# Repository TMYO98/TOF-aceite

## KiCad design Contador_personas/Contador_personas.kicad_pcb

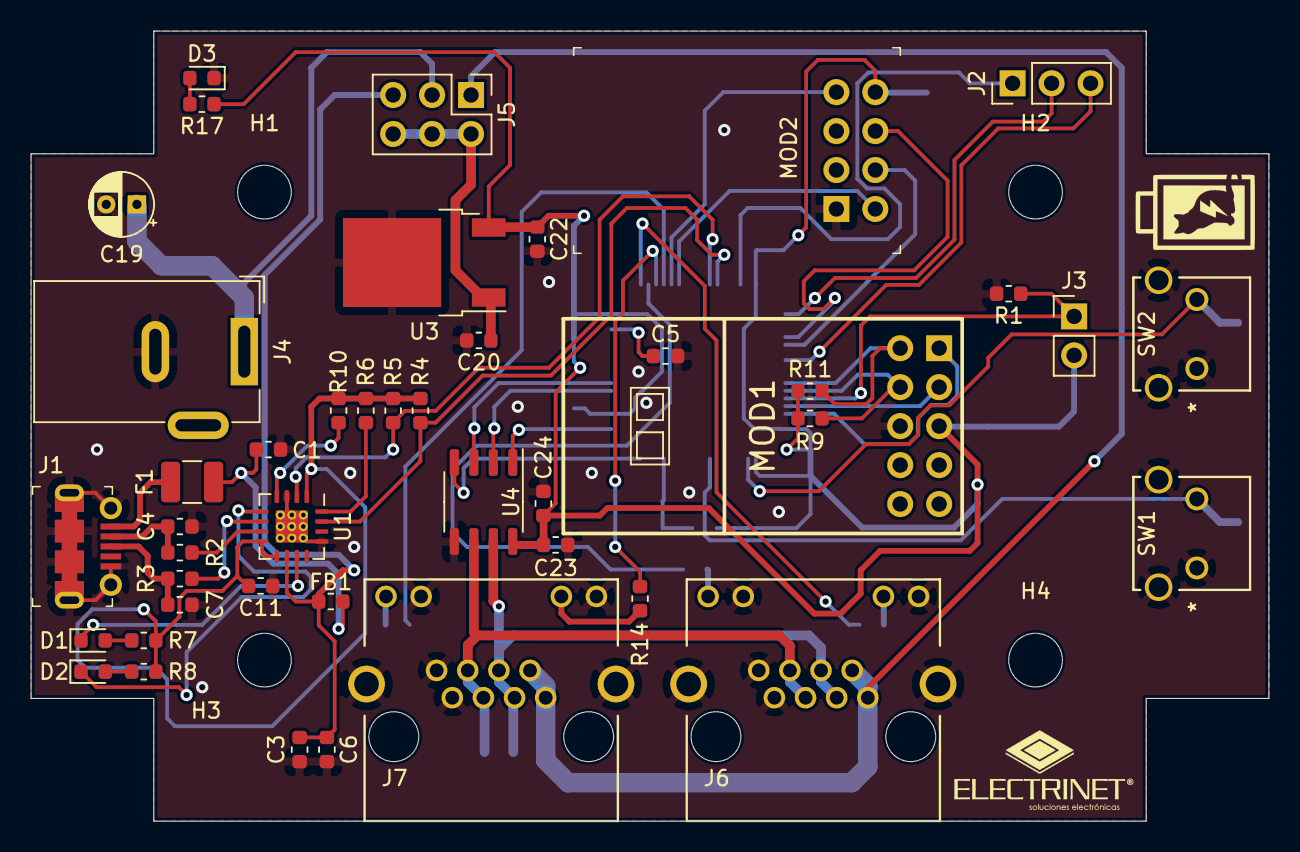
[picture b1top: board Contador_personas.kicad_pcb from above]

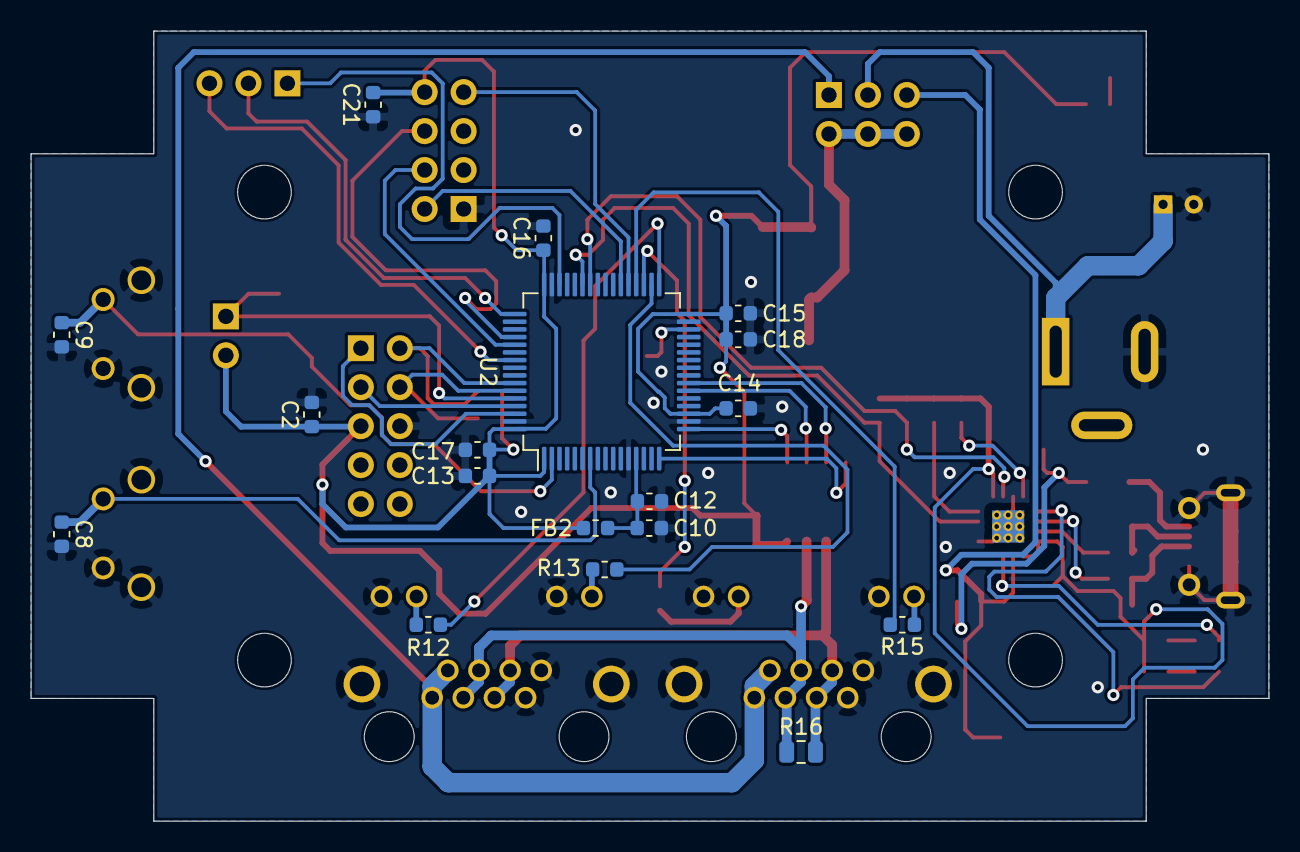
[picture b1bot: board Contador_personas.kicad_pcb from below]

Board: 2 copper layers, 80.7 x 51.5 mm, 66 parts (18 on the bottom side), 52 nets.

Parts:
C1: 10nF; C_0603_1608Metric
C2, C6, C8, C9, C10, C11, C12, C13, C14, C15, C16, C17, C21, C24: 0.1uF; C_0603_1608Metric
C3, C5, C18: 4.7uF; C_0603_1608Metric
C4, C7: 47pF; C_0603_1608Metric
C19: 10uF; CP_Radial_D4.0mm_P2.00mm
C20, C23: 1uF; C_0603_1608Metric
C22: 2.2uF; C_0603_1608Metric
D1, D2, D3: LED; LED_0603_1608Metric
F1: 0ZCH0050FF2G; Fuse_1210_3225Metric
FB1: BLM21PG221SN1D; R_0603_1608Metric
FB2: BK1608TS601-T; R_0603_1608Metric
H1, H2, H3, H4: MountingHole; MountingHole_3.5mm
J1: 1050170001; USB_Micro_B_Female_1050170001
J2: Conn_01x03_Male; PinHeader_1x03_P2.54mm_Vertical
J3: Conn_01x02_Male; PinHeader_1x02_P2.54mm_Vertical
J4: 694106301002‎; BarrelJack_Wuerth_6941xx301002
J5: Conn_02x03_Odd_Even; PinHeader_2x03_P2.54mm_Vertical
J6, J7: RJHSE-5381
MOD1: VL53L1X-SATEL; VL53L1X_SATEL
MOD2: WRL-17146; Wifi_Module_ESP8266_WRL-13678
R1, R4, R5, R6, R10: 10K; R_0603_1608Metric
R2, R3: 27; R_0603_1608Metric
R7, R8, R12, R13, R14, R15: 270; R_0603_1608Metric
R9, R11: 4.7K; R_0603_1608Metric
R16: 120; R_0805_2012Metric
R17: 1K; R_0603_1608Metric
SW1, SW2: 1825027-5
U1: FT230XQ; QFN-16-1EP_4x4mm_P0.65mm_EP2.1x2.1mm_ThermalVias
U2: STM32F401RETx; LQFP-64_10x10mm_P0.5mm
U3: LDF33DT-TR; TO-252-2
U4: ST3485EIDT‎; SO-8_3.9x4.9mm_P1.27mm

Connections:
+3V3: C2.1, C13.1, C14.1, C15.1, C16.1, C17.1, C18.2, C21.2, C22.1, C23.1, C24.1, FB2.2, J3.2, MOD1.5, MOD2.8, R9.1, R11.1, R17.1, U2.1, U2.19, U2.32, U2.48, U2.64, U3.3, U4.8
+5V: C3.1, C6.1, FB1.1, J5.5, U1.10
+9V: C19.1, J4.1, J5.3
+12V: J5.1, J6.1, J6.2, J7.1, J7.2
+VDC: C20.1, J5.2, J5.4, J5.6, U3.1
A: J6.5, J6.6, J7.5, J7.6, R16.2, U4.6
B: J6.3, J6.4, J7.3, J7.4, R16.1, U4.7
CHPD: MOD2.4, U2.53
DE: U2.23, U4.3
GND: C1.2, C2.2, C3.2, C4.2, C5.2, C6.2, C7.2, C8.2, C9.2, C10.2, C11.1, C12.2, C13.2, C14.2, C15.2, C16.2, C17.2, C18.1, C19.2, C20.2, C21.1, C22.2, C23.2, C24.2, D3.1, J1.5, J1.SH, J4.2, J6.7, J6.8, J6.9, J6.11, J6.S1, J6.S2, J7.7, J7.8, J7.9, J7.11, J7.S1, J7.S2, MOD1.6, MOD2.1, R1.2, SW1.1, SW1.3, SW1.4, SW2.1, SW2.3, SW2.4, U1.3, U1.13, U1.17, U2.12, U2.18, U2.31, U2.47, U2.63, U3.2, U4.5
I2C1_SCL: MOD1.2, R11.2, U2.58
I2C1_SDA: MOD1.4, R9.2, U2.59
INT: MOD1.1, U2.62
LED_1_DI: R12.2, U2.33
LED_1_DO: R13.2, U2.34
LED_2_DI: R14.2, U2.35
LED_2_DO: R15.2, U2.36
unnamed: C1.1, F1.1, FB1.2
unnamed: C4.1, J1.2, R2.2
unnamed: C5.1, U2.30
unnamed: C7.1, J1.3, R3.2
unnamed: C8.1, SW1.2, U2.7
unnamed: C9.1, SW2.2, U2.2
unnamed: C10.1, C12.1, FB2.1, U2.13
unnamed: C11.2, R4.1, R5.1, R6.1, R7.1, R8.1, R10.1, U1.1, U1.8, U1.9
unnamed: D1.1, U1.11
unnamed: D1.2, R7.2
unnamed: D2.1, U1.5
unnamed: D2.2, R8.2
unnamed: D3.2, R17.2
unnamed: F1.2, J1.1
unnamed: J3.1, R1.1, U2.60
unnamed: J6.10, R12.1
unnamed: J6.12, R13.1
unnamed: J7.10, R14.1
unnamed: J7.12, R15.1
unnamed: R2.1, U1.7
unnamed: R3.1, U1.6
unnamed: R6.2, U1.16
unnamed: R10.2, U1.4
RST: MOD2.6, U2.52
SWCLK: J2.2, U2.49
SWDIO: J2.1, U2.46
SWO: J2.3, U2.55
USART1_RX: R4.2, U1.15, U2.43
USART1_TX: R5.2, U1.2, U2.42
USART2_RX: U2.17, U4.1
USART2_TX: U2.16, U4.4
USART6_RX: MOD2.2, U2.38
USART6_TX: MOD2.7, U2.37
XSDN: MOD1.3, U2.61
~RE: U2.22, U4.2

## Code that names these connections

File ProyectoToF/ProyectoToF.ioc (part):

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Mcu.Name=STM32F401R(D-E)Tx
Mcu.Package=LQFP64
Mcu.UserName=STM32F401RETx
PA10.Mode=Asynchronous
PA10.Signal=USART1_RX
PA13.GPIOParameters=GPIO_Label
PA13.GPIO_Label=SDIO
PA13.Signal=SYS_JTMS-SWDIO
PA14.GPIOParameters=GPIO_Label
PA14.GPIO_Label=SCLK
PA14.Signal=SYS_JTCK-SWCLK
PA2.Mode=Asynchronous
PA2.Signal=USART2_TX
PA3.Mode=Asynchronous
PA3.Signal=USART2_RX
PA6.GPIOParameters=GPIO_Label
PA6.GPIO_Label=RE
PA6.Signal=GPIO_Output
PA7.GPIOParameters=GPIO_Label
PA7.GPIO_Label=DE
PA7.Signal=GPIO_Output
PA9.Mode=Asynchronous
PA9.Signal=USART1_TX
PB12.GPIOParameters=GPIO_Speed,GPIO_Label
PB12.GPIO_Label=LED_1_DI
PB12.GPIO_Speed=GPIO_SPEED_FREQ_LOW
PB12.Signal=GPIO_Output
PB13.GPIOParameters=GPIO_Label
PB13.GPIO_Label=LED_1_DO
PB13.Signal=GPIO_Output
PB14.GPIOParameters=GPIO_Label
PB14.GPIO_Label=LED_2_DI
PB14.Signal=GPIO_Output
PB15.GPIOParameters=GPIO_Label
PB15.GPIO_Label=LED_2_DO
PB15.Signal=GPIO_Output
PB3.GPIOParameters=GPIO_Label
PB3.GPIO_Label=SWO
PB3.Signal=SYS_JTDO-SWO
PB6.GPIOParameters=GPIO_Pu
PB6.GPIO_Pu=GPIO_PULLUP
PB6.Mode=I2C
PB6.Signal=I2C1_SCL
PB7.GPIOParameters=GPIO_Pu
PB7.GPIO_Pu=GPIO_PULLUP
PB7.Mode=I2C
PB7.Signal=I2C1_SDA
PB8.GPIOParameters=GPIO_PuPd,GPIO_Label
PB8.GPIO_Label=XSDN
PB8.GPIO_PuPd=GPIO_NOPULL
PB8.Signal=GPIO_Output
PB9.GPIOParameters=GPIO_PuPd,GPIO_Label
PB9.GPIO_Label=INT
PB9.GPIO_PuPd=GPIO_PULLUP
PB9.Signal=GPXTI9
PC11.GPIOParameters=GPIO_Label
PC11.GPIO_Label=RST
PC11.Signal=GPIO_Output
PC12.GPIOParameters=GPIO_Label
PC12.GPIO_Label=CHPD
PC12.Signal=GPIO_Output
PC6.Signal=GPIO_Output
RCC.HSE_VALUE=25000000
RCC.SYSCLKFreq_VALUE=16000000
board=custom

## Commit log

2023-04-10 Proyecto entero
2023-05-05 Actualizacion Tamayo

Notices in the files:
parts and their libraries:
Copyright 2016 Accelerated Designs. All rights reserved.
